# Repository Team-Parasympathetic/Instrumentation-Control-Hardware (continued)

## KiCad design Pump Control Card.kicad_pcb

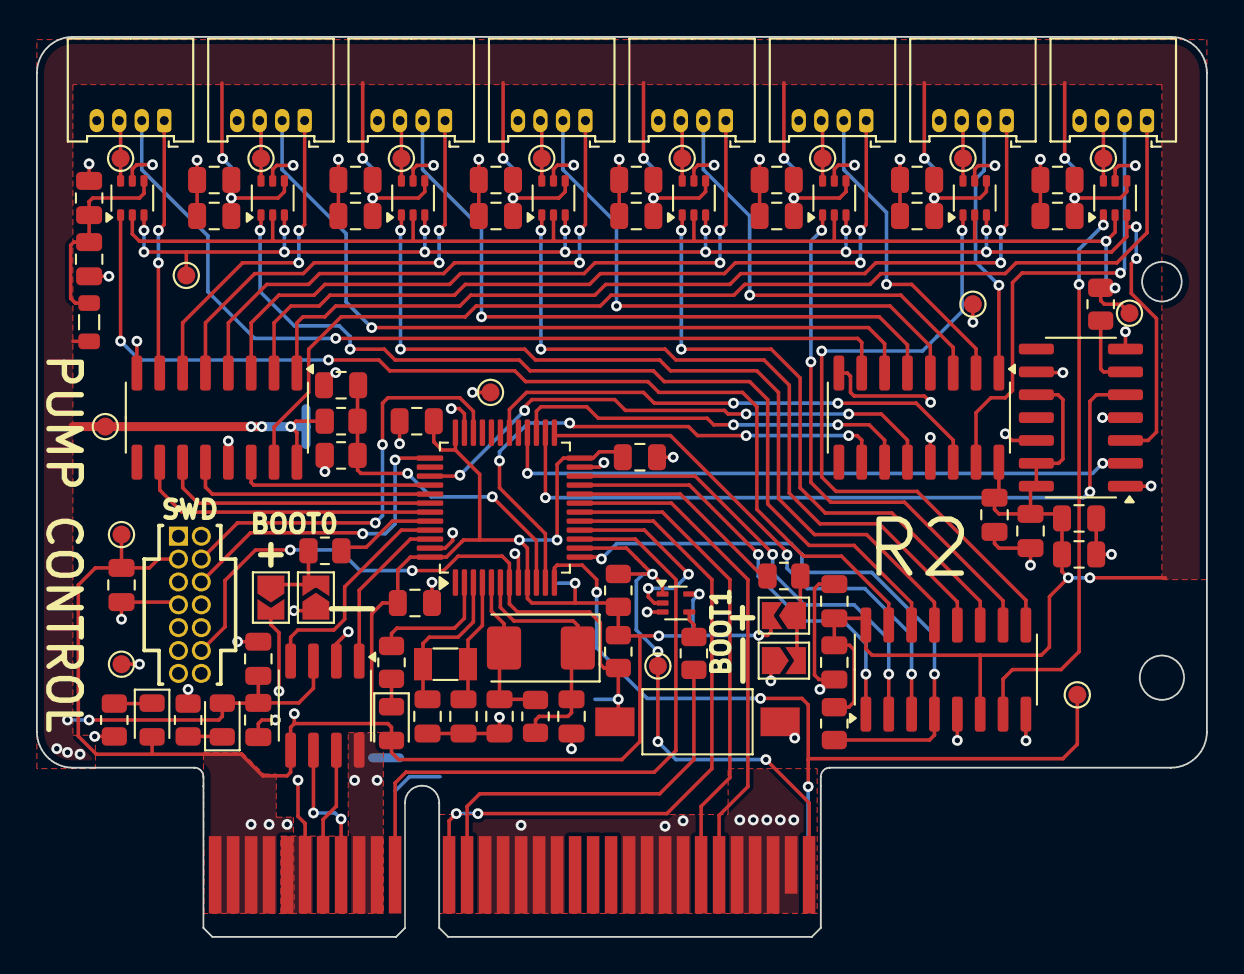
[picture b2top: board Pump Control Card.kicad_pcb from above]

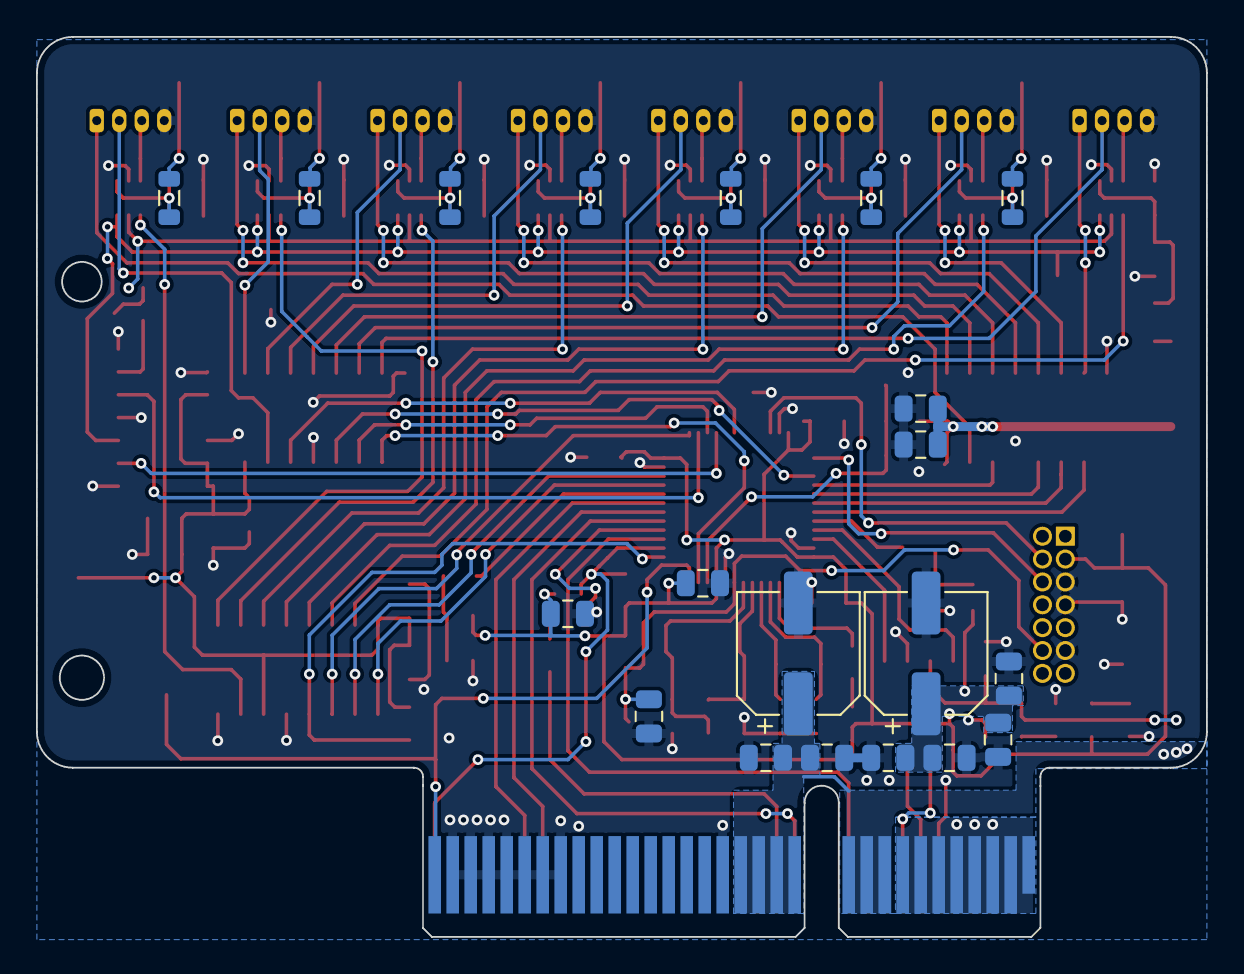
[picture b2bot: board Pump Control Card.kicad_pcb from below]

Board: 2 copper layers, 65.0 x 50.0 mm, 119 parts (20 on the bottom side), 89 nets.

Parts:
C1, C2, C6, C8, C10, C14, C16, C21, C22, C23, C25, C27, C29, C31, C33, C35, C37, C39, C41, C88, C91, C125: 0.1uF; C_0805_2012Metric
C3: 47nF; C_0805_2012Metric
C7, C9, C11, C15, C24, C26, C28, C30, C32, C34, C36, C38, C40, C89, C93: 1uF; C_0805_2012Metric
C12, C13: 10uF; C_0805_2012Metric
C17, C18, C19, C20: 20pF; C_0805_2012Metric
C90, C96: 47uF; CP_Elec_6.3x5.9
D2, D3, D4: LED; LED_0805_2012Metric
FB1, FB2, FB3, FB4, FB5, FB6, FB7, FB8: FerriteBead_Small; L_0805_2012Metric
J1, J2, J4, J5, J6, J7, J8, J9: Conn_01x04; Molex_PicoBlade_53048-0410_1x04_P1.25mm_Horizontal
J3: FTSH-107-01-L-D-K; SAMTEC_FTSH-107-01-L-D-K
J10: 10018784-10201TLF; BUS_PCIexpress_x4
JP5, JP6, JP7, JP8: SolderJumper_2_Open; SolderJumper-2_P1.3mm_Open_TrianglePad1.0x1.5mm
R1, R6: 22R; R_0805_2012Metric
R2, R11: 510R; R_0805_2012Metric
R3: 1K; R_0805_2012Metric
R4, R5: 4.7K; R_0805_2012Metric
R7: 33K; R_0805_2012Metric
R8: 20K; R_0805_2012Metric
R12: 10K; R_0805_2012Metric
R13, R14: 100K; R_0805_2012Metric
R15: 1M; R_0805_2012Metric
SW2: SW_Push; SW_SPST_FSMSM
TP1, TP2, TP3, TP4, TP5, TP6, TP7, TP8, TP9, TP10, TP11, TP12, TP13, TP14, TP15, TP16, TP17: TestPoint; TestPoint_Pad_D1.0mm
U1: MCP2562-E-SN; SOIC-8_3.9x4.9mm_P1.27mm
U2: SN74LVC1G125DRL; Texas_R-PDSO-N5_DRL-5
U3, U5: 74HCT595; SOIC-16_3.9x9.9mm_P1.27mm
U4: STM32F103C8Tx; LQFP-48_7x7mm_P0.5mm
U6: 74AHCT125; SOIC-14_3.9x8.7mm_P1.27mm
U7, U9, U10, U11, U12, U13, U14, U15: DAC7311xDCK; SOT-363_SC-70-6
U8: 74HCT138; SOIC-16_3.9x9.9mm_P1.27mm
Y3: 8MHz; Crystal_SMD_Abracon_ABM3-2Pin_5.0x3.2mm
Y4: 32.768K; Crystal_SMD_3215-2Pin_3.2x1.5mm

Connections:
+3V3: C2.1, C6.2, C13.1, C16.1, C21.1, C22.1, C23.1, C88.1, C89.1, C90.1, C125.1, D2.2 (A), D4.2 (A), J3.03, J10.A1, J10.A2, J10.A3, J10.A4, J10.A5, J10.A6, J10.A7, J10.A8, J10.B1, J10.B2, J10.B3, J10.B4, JP5.2 (B), JP7.2 (B), R4.1, R12.1, TP3.1, U1.5 (Vio), U2.5 (VCC), U4.9 (VDDA), U4.24 (VDD), U4.36 (VDD), U4.48 (VDD)
+5V: C1.1, C7.1, C8.1, C9.1, C10.1, C12.1, C24.1, C25.1, C26.1, C27.1, C91.1, C93.1, C96.1, D3.2 (A), FB1.1, FB2.1, FB3.1, FB4.1, FB5.1, FB6.1, FB7.1, FB8.1, J10.A9, J10.A10, J10.A11, J10.A12, J10.A13, J10.A14, J10.A15, R5.1, R7.1, TP2.1, U1.3 (VDD), U3.16 (VCC), U5.16 (VCC), U6.10, U6.13, U6.14 (VCC), U8.6 (E2), U8.16 (VCC)
/CAN_H: J10.B7, U1.7 (CANH)
/CAN_L: J10.B8, U1.6 (CANL)
/CS: J10.B32, R4.2, TP16.1, U2.1, U4.14 (PA4)
/DAC_Array/CS_1: U8.15 (~Y0), U15.1 (~SYNC)
/DAC_Array/CS_2: U8.14 (~Y1), U14.1 (~SYNC)
/DAC_Array/CS_3: U8.13 (~Y2), U13.1 (~SYNC)
/DAC_Array/CS_4: U8.12 (~Y3), U12.1 (~SYNC)
/DAC_Array/CS_5: U8.11 (~Y4), U11.1 (~SYNC)
/DAC_Array/CS_6: U8.10 (~Y5), U10.1 (~SYNC)
/DAC_Array/CS_7: U8.9 (~Y6), U9.1 (~SYNC)
/DAC_Array/CS_8: U7.1 (~SYNC), U8.7 (~Y7)
/DIR_1: J9.2, U5.15 (QA)
/DIR_2: J8.2, U5.1 (QB)
/DIR_3: J7.2, U5.2 (QC)
/DIR_4: J6.2, U5.3 (QD)
/DIR_5: J5.2, U5.4 (QE)
/DIR_6: J4.2, U5.5 (QF)
/DIR_7: J2.2, U5.6 (QG)
/DIR_8: J1.2, U5.7 (QH)
/Decoder/A0: U4.21 (PB10), U8.1 (A0)
/Decoder/A1: U4.22 (PB11), U8.2 (A1)
/Decoder/A2: U4.25 (PB12), U8.3 (A2)
/Decoder/EN: R5.2, U4.13 (PA3), U8.4 (~E0)
/EN_1: J9.1, U3.15 (QA)
/EN_2: J8.1, U3.1 (QB)
/EN_3: J7.1, U3.2 (QC)
/EN_4: J6.1, U3.3 (QD)
/EN_5: J5.1, U3.4 (QE)
/EN_6: J4.1, U3.5 (QF)
/EN_7: J2.1, U3.6 (QG)
/EN_8: J1.1, U3.7 (QH)
/IRQ: J10.A32, TP17.1, U4.12 (PA2)
/Level Shifter/IN0: U4.28 (PB15), U6.2
/Level Shifter/IN1: U4.26 (PB13), U6.5
/Level Shifter/OUT1: R6.1, U6.6
/MCU/CANRX: U1.4 (RXD), U4.45 (PB8)
/MCU/CANTX: U1.1 (TXD), U4.46 (PB9)
/MCU/MISO_1: U2.2, U4.16 (PA6)
/MCU/MOSI_1: J10.B12, U4.17 (PA7)
/MCU/NRST: C15.1, J3.12, R12.2, SW2.2, U4.7 (NRST)
/MCU/PA1: U4.11 (PA1), U5.10 (~SRCLR)
/MCU/PA9: U4.30 (PA9), U5.14 (SER)
/MCU/PB3: U4.39 (PB3), U5.12 (RCLK)
/MCU/PB4: U3.14 (SER), U4.40 (PB4)
/MCU/PB5: U3.12 (RCLK), U4.41 (PB5)
/MCU/PB6: U3.11 (SRCLK), U4.42 (PB6)
/MCU/PB7: U3.10 (~SRCLR), U4.43 (PB7)
/MCU/PB14: U4.27 (PB14), U5.11 (SRCLK)
/MCU/PC13: R11.2, U4.2 (PC13)
/MCU/SCK_1: J10.B11, U4.15 (PA5)
/MCU/SWCLK: J3.06, U4.37 (PA14)
/MCU/SWDIO: J3.04, U4.34 (PA13)
/MCU/VSENS: C3.1, R7.2, R8.1, U4.10 (PA0)
/PCIE/MISO_1: J10.B13, R1.1
/RST: J10.B26, U4.18 (PB0)
/SPD_1: J9.3, TP4.1, U7.6 (VOUT)
/SPD_2: J8.3, TP5.1, U9.6 (VOUT)
/SPD_3: J7.3, TP6.1, U10.6 (VOUT)
/SPD_4: J6.3, TP7.1, U11.6 (VOUT)
/SPD_5: J5.3, TP8.1, U12.6 (VOUT)
/SPD_6: J4.3, TP9.1, U13.6 (VOUT)
/SPD_7: J2.3, TP10.1, U14.6 (VOUT)
/SPD_8: J1.3, TP11.1, U15.6 (VOUT)
/SPI2_MOSI: TP12.1, U6.3, U7.3 (DIN), U9.3 (DIN), U10.3 (DIN), U11.3 (DIN), U12.3 (DIN), U13.3 (DIN), U14.3 (DIN), U15.3 (DIN)
/SPI2_SCK: R6.2, TP13.1, U7.2 (SCLK), U9.2 (SCLK), U10.2 (SCLK), U11.2 (SCLK), U12.2 (SCLK), U13.2 (SCLK), U14.2 (SCLK), U15.2 (SCLK)
/SYNC: J10.B27, U4.19 (PB1)
/Tristate/OUT: R1.2, U2.4
GND: C1.2, C2.2, C3.2, C6.1, C7.2, C8.2, C9.2, C10.2, C11.2, C12.2, C13.2, C14.2, C15.2, C16.2, C17.1, C18.1, C19.1, C20.1, C21.2, C22.2, C23.2, C24.2, C25.2, C26.2, C27.2, C28.2, C29.2, C30.2, C31.2, C32.2, C33.2, C34.2, C35.2, C36.2, C37.2, C38.2, C39.2, C40.2, C41.2, C88.2, C89.2, C90.2, C91.2, C93.2, C96.2, C125.2, J1.4, J2.4, J3.05, J3.07, J3.11, J4.4, J5.4, J6.4, J7.4, J8.4, J9.4, J10.A16, J10.A25, J10.A26, J10.A27, J10.A28, J10.A29, J10.A30, J10.A31, J10.B5, J10.B6, J10.B9, J10.B10, J10.B14, J10.B15, J10.B16, J10.B17, J10.B18, J10.B22, J10.B23, J10.B24, J10.B25, J10.B28, J10.B29, J10.B30, J10.B31, JP6.1 (A), JP8.1 (A), R2.2, R3.2, R8.2, SW2.1, TP1.1, TP14.1, TP15.1, U1.2 (VSS), U1.8 (STBY), U2.3 (GND), U3.8 (GND), U3.13 (~OE), U4.8 (VSSA), U4.23 (VSS), U4.35 (VSS), U4.47 (VSS), U5.8 (GND), U5.13 (~OE), U6.1, U6.4, U6.7 (GND), U6.9, U6.12, U7.5 (GND), U8.5 (~E1), U8.8 (GND), U9.5 (GND), U10.5 (GND), U11.5 (GND), U12.5 (GND), U13.5 (GND), U14.5 (GND), U15.5 (GND)
unnamed: D2.1 (K), R2.1
unnamed: D3.1 (K), R3.1
unnamed: D4.1 (K), R11.1
unnamed: JP5.1 (A), JP6.2 (B), R14.1
unnamed: JP7.1 (A), JP8.2 (B), R13.1
unnamed: R13.2, U4.44 (BOOT0)
unnamed: R14.2, U4.20 (PB2)
unnamed: C19.2, U4.3 (PC14), Y4.2
unnamed: C20.2, U4.4 (PC15), Y4.1
unnamed: C17.2, R15.1, U4.5 (PD0), Y3.2
unnamed: C18.2, R15.2, U4.6 (PD1), Y3.1
unnamed: C11.1, C14.1, FB1.2, U7.4 (AVDD/AVREF)
unnamed: C28.1, C29.1, FB2.2, U9.4 (AVDD/AVREF)
unnamed: C30.1, C31.1, FB3.2, U10.4 (AVDD/AVREF)
unnamed: C32.1, C33.1, FB4.2, U11.4 (AVDD/AVREF)
unnamed: C34.1, C35.1, FB5.2, U12.4 (AVDD/AVREF)
unnamed: C36.1, C37.1, FB6.2, U13.4 (AVDD/AVREF)
unnamed: C38.1, C39.1, FB7.2, U14.4 (AVDD/AVREF)
unnamed: C40.1, C41.1, FB8.2, U15.4 (AVDD/AVREF)

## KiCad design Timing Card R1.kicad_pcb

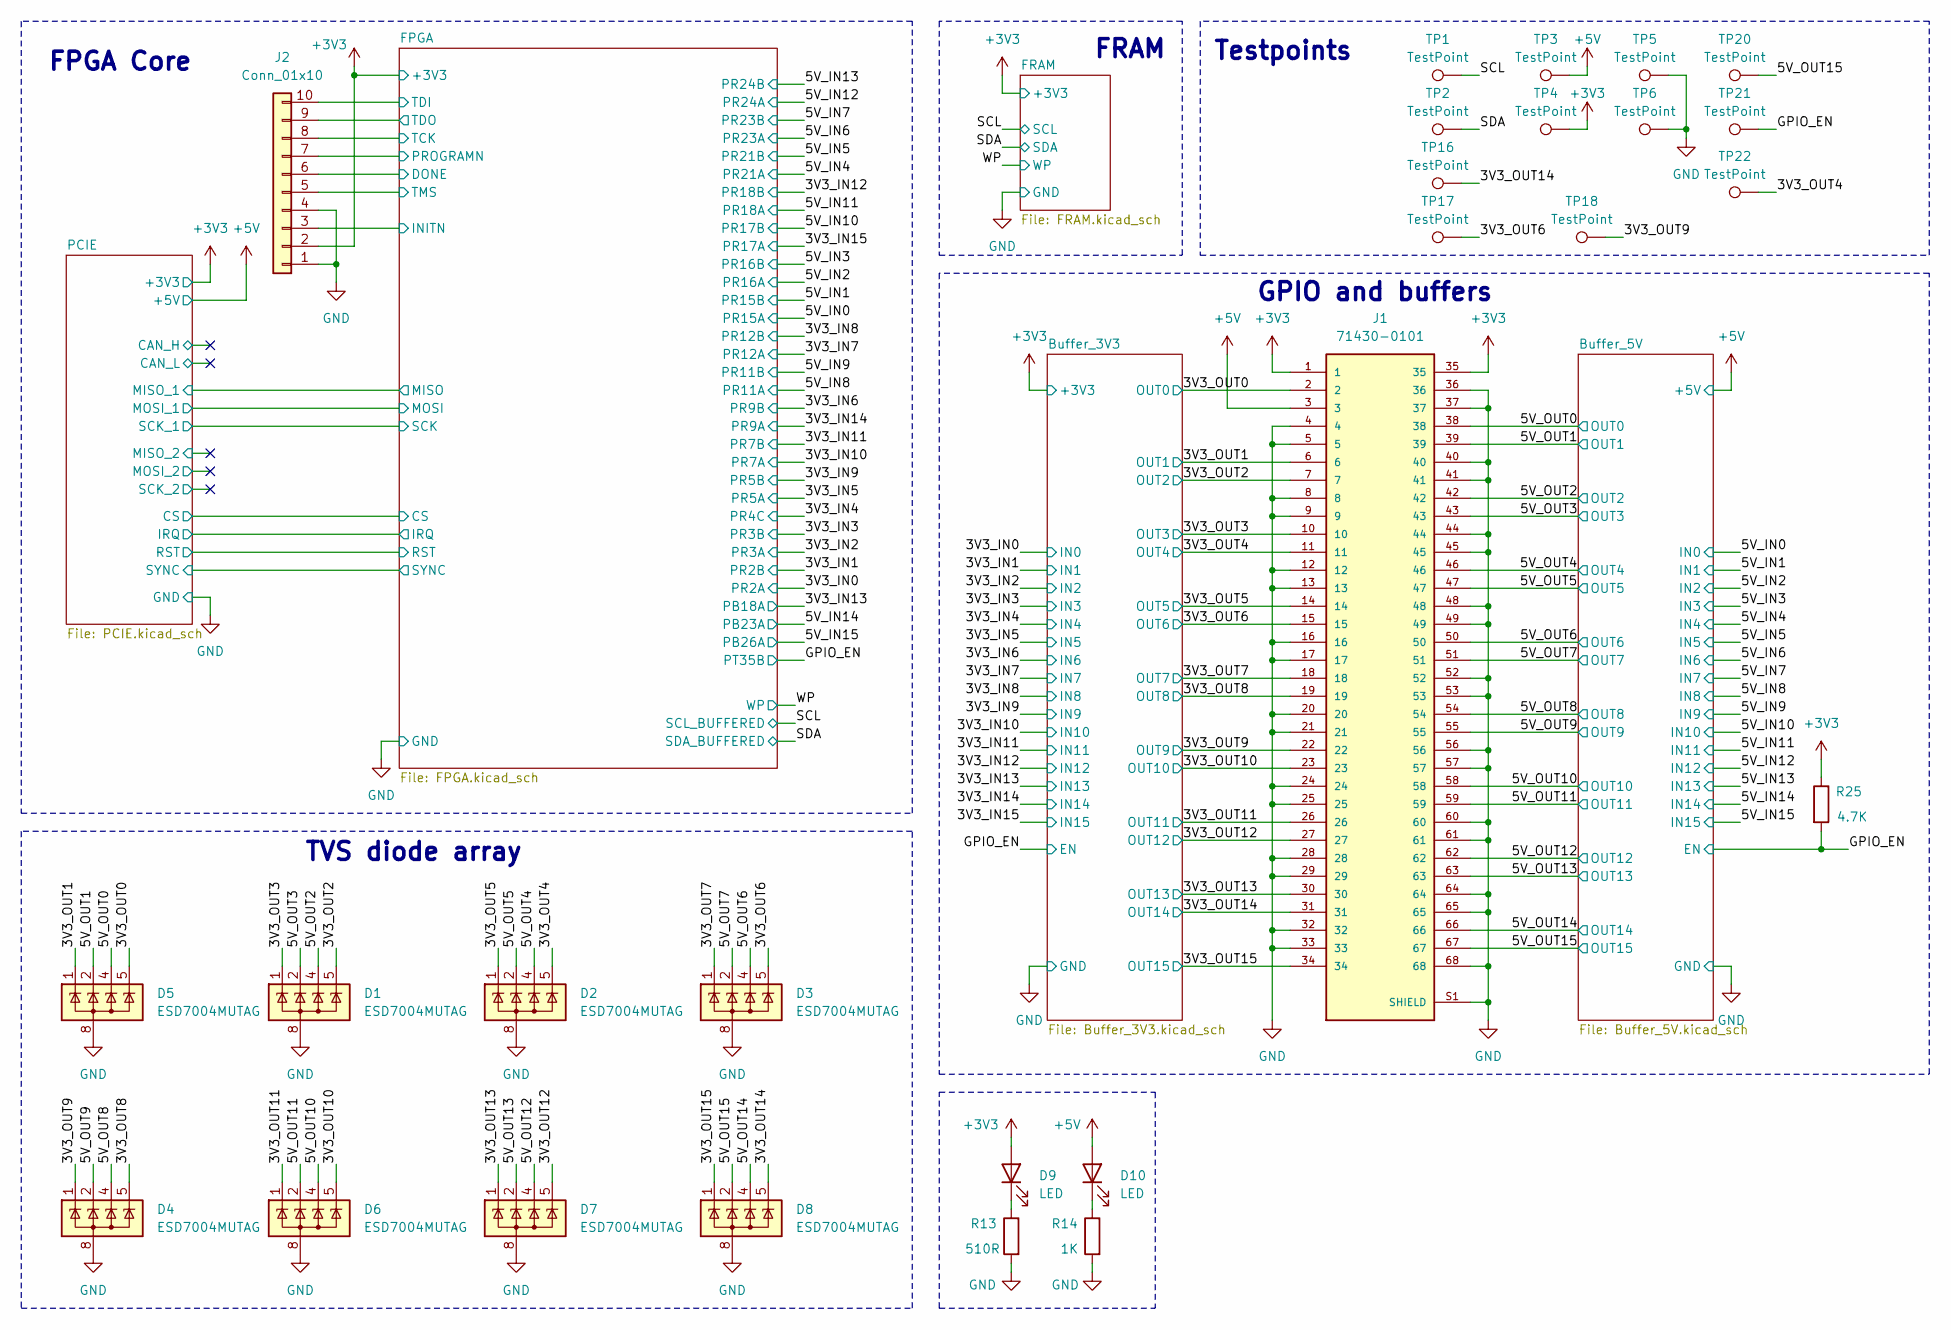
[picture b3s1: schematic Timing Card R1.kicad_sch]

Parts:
D1, D2, D3, D4, D5, D6, D7, D8: ESD7004MUTAG; Diodes_UDFN-10_1x2.5mm_P0.5mm_Modified
D9, D10: LED; LED_0805_2012Metric
J1: 71430-0101; MOLEX_71430-0101; PARTREV N
J2: Conn_01x10; PinHeader_2x05_P2.54mm_Vertical
R13: 510R; R_0805_2012Metric
R14: 1K; R_0805_2012Metric
R25: 4.7K; R_0805_2012Metric
TP1, TP2, TP3, TP4, TP5, TP6, TP16, TP17, TP18, TP20, TP21, TP22: TestPoint; TestPoint_Pad_D1.0mm

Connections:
+5V: D10.2 (A), J1.3, TP3.1; also elsewhere on the board
/3V3_OUT0: D5.5 (K), J1.2; also elsewhere on the board
/3V3_OUT1: D5.1 (K), J1.6; also elsewhere on the board
/3V3_OUT2: D1.5 (K), J1.7; also elsewhere on the board
/3V3_OUT3: D1.1 (K), J1.10; also elsewhere on the board
/3V3_OUT4: D2.5 (K), J1.11, TP22.1; also elsewhere on the board
/3V3_OUT5: D2.1 (K), J1.14; also elsewhere on the board
/3V3_OUT6: D3.5 (K), J1.15, TP17.1; also elsewhere on the board
/3V3_OUT7: D3.1 (K), J1.18; also elsewhere on the board
/3V3_OUT8: D4.5 (K), J1.19; also elsewhere on the board
/3V3_OUT9: D4.1 (K), J1.22, TP18.1; also elsewhere on the board
/3V3_OUT10: D6.5 (K), J1.23; also elsewhere on the board
/3V3_OUT11: D6.1 (K), J1.26; also elsewhere on the board
/3V3_OUT12: D7.5 (K), J1.27; also elsewhere on the board
/3V3_OUT13: D7.1 (K), J1.30; also elsewhere on the board
/3V3_OUT14: D8.5 (K), J1.31, TP16.1; also elsewhere on the board
/3V3_OUT15: D8.1 (K), J1.34; also elsewhere on the board
/5V_OUT0: D5.4 (K), J1.38; also elsewhere on the board
/5V_OUT1: D5.2 (K), J1.39; also elsewhere on the board
/5V_OUT2: D1.4 (K), J1.42; also elsewhere on the board
/5V_OUT3: D1.2 (K), J1.43; also elsewhere on the board
/5V_OUT4: D2.4 (K), J1.46; also elsewhere on the board
/5V_OUT5: D2.2 (K), J1.47; also elsewhere on the board
/5V_OUT6: D3.4 (K), J1.50; also elsewhere on the board
/5V_OUT7: D3.2 (K), J1.51; also elsewhere on the board
/5V_OUT8: D4.4 (K), J1.54; also elsewhere on the board
/5V_OUT9: D4.2 (K), J1.55; also elsewhere on the board
/5V_OUT10: D6.4 (K), J1.58; also elsewhere on the board
/5V_OUT11: D6.2 (K), J1.59; also elsewhere on the board
/5V_OUT12: D7.4 (K), J1.62; also elsewhere on the board
/5V_OUT13: D7.2 (K), J1.63; also elsewhere on the board
/5V_OUT14: D8.4 (K), J1.66; also elsewhere on the board
/5V_OUT15: D8.2 (K), J1.67, TP20.1; also elsewhere on the board
/FPGA/DONE: J2.6; also elsewhere on the board
/FPGA/INITN: J2.3; also elsewhere on the board
/FPGA/PROGRAMN: J2.7; also elsewhere on the board
/FPGA/TCK: J2.8; also elsewhere on the board
/FPGA/TDI: J2.10; also elsewhere on the board
/FPGA/TDO: J2.9; also elsewhere on the board
/FPGA/TMS: J2.5; also elsewhere on the board
/GPIO_EN: R25.2, TP21.1; also elsewhere on the board
/SCL: TP1.1; also elsewhere on the board
/SDA: TP2.1; also elsewhere on the board
unnamed: D9.1 (K), R13.1
unnamed: D10.1 (K), R14.1

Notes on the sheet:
FRAM
FPGA Core
Testpoints
GPIO and buffers
TVS diode array

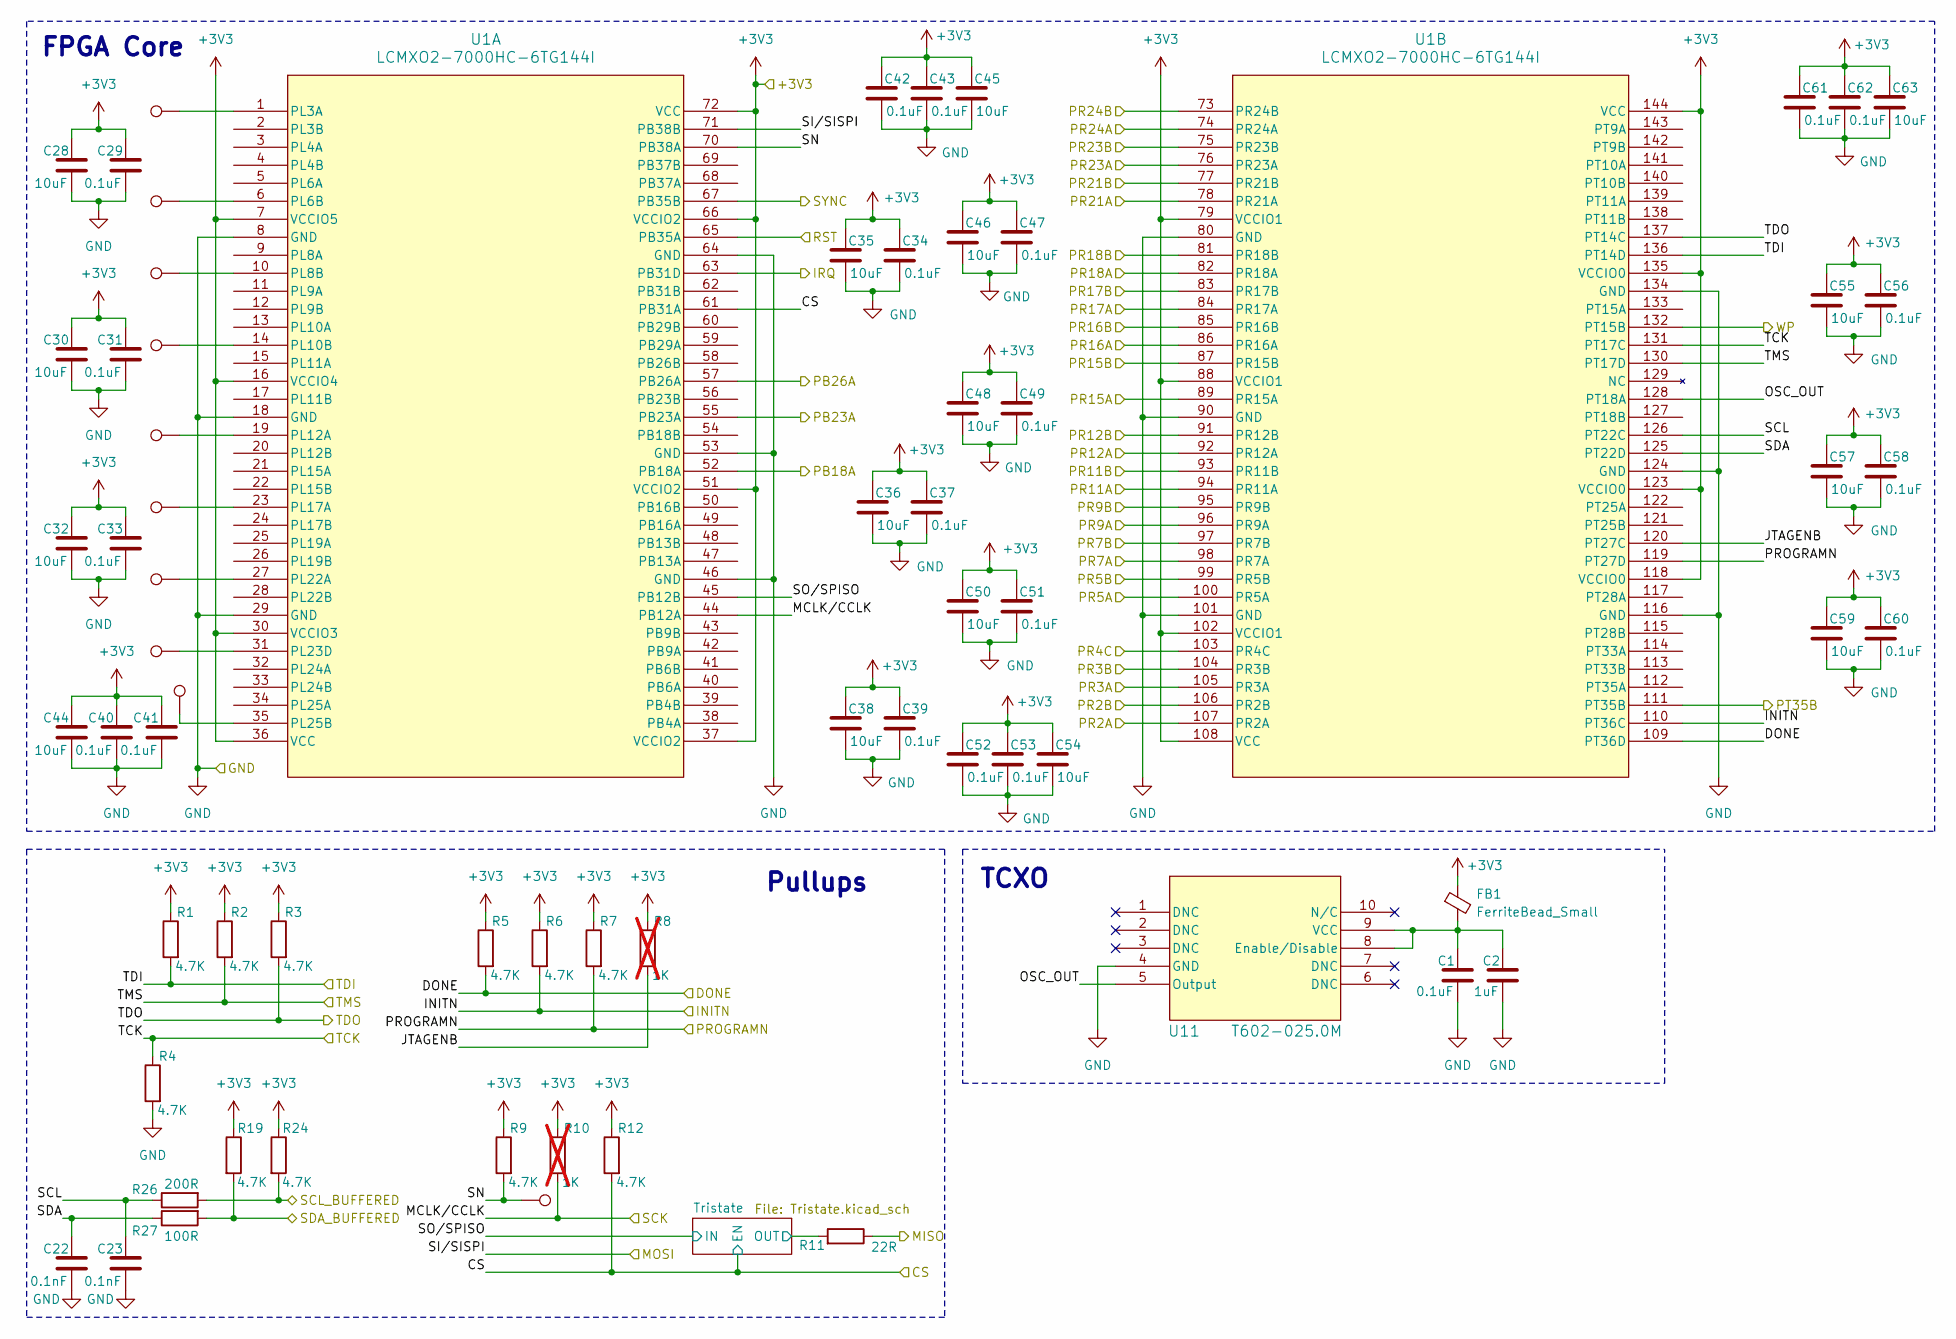
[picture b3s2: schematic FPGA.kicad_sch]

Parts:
C1: 0.1uF; C_0805_2012Metric
C2: 1uF; C_0805_2012Metric
C22, C23: 0.1nF; C_0805_2012Metric
C28, C30, C32, C35, C36, C38, C44, C45, C46, C48, C50, C54, C55, C57, C59, C63: 10uF; C_0603_1608Metric
C29, C31, C33, C34, C37, C39, C40, C41, C42, C43, C47, C49, C51, C52, C53, C56, C58, C60, C61, C62: 0.1uF; C_0603_1608Metric
FB1: FerriteBead_Small; L_0805_2012Metric
R1, R2, R3, R4, R5, R6, R7, R9, R12, R19, R24: 4.7K; R_0805_2012Metric
R8, R10: 1K; R_0805_2012Metric; not fitted
R11: 22R; R_0805_2012Metric
R26: 200R; R_0805_2012Metric
R27: 100R; R_0805_2012Metric
TP7, TP8, TP9, TP10, TP11, TP12, TP13, TP14, TP15: TestPoint; TestPoint_Pad_1.0x1.0mm
TP19: TestPoint; TestPoint_Pad_D1.0mm
U1: LCMXO2-7000HC-6TG144I; TQFP144_LAT
U11: T602-025.0M; T602-025.0M_CNW

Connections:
/3V3_IN0: U1.107 (PR2A); also elsewhere on the board
/3V3_IN1: U1.106 (PR2B); also elsewhere on the board
/3V3_IN2: U1.105 (PR3A); also elsewhere on the board
/3V3_IN3: U1.104 (PR3B); also elsewhere on the board
/3V3_IN4: U1.103 (PR4C); also elsewhere on the board
/3V3_IN5: U1.100 (PR5A); also elsewhere on the board
/3V3_IN6: U1.95 (PR9B); also elsewhere on the board
/3V3_IN7: U1.92 (PR12A); also elsewhere on the board
/3V3_IN8: U1.91 (PR12B); also elsewhere on the board
/3V3_IN9: U1.99 (PR5B); also elsewhere on the board
/3V3_IN10: U1.98 (PR7A); also elsewhere on the board
/3V3_IN11: U1.97 (PR7B); also elsewhere on the board
/3V3_IN12: U1.81 (PR18B); also elsewhere on the board
/3V3_IN13: U1.52 (PB18A); also elsewhere on the board
/3V3_IN14: U1.96 (PR9A); also elsewhere on the board
/3V3_IN15: U1.84 (PR17A); also elsewhere on the board
/5V_IN0: U1.89 (PR15A); also elsewhere on the board
/5V_IN1: U1.87 (PR15B); also elsewhere on the board
/5V_IN2: U1.86 (PR16A); also elsewhere on the board
/5V_IN3: U1.85 (PR16B); also elsewhere on the board
/5V_IN4: U1.78 (PR21A); also elsewhere on the board
/5V_IN5: U1.77 (PR21B); also elsewhere on the board
/5V_IN6: U1.76 (PR23A); also elsewhere on the board
/5V_IN7: U1.75 (PR23B); also elsewhere on the board
/5V_IN8: U1.94 (PR11A); also elsewhere on the board
/5V_IN9: U1.93 (PR11B); also elsewhere on the board
/5V_IN10: U1.83 (PR17B); also elsewhere on the board
/5V_IN11: U1.82 (PR18A); also elsewhere on the board
/5V_IN12: U1.74 (PR24A); also elsewhere on the board
/5V_IN13: U1.73 (PR24B); also elsewhere on the board
/5V_IN14: U1.55 (PB23A); also elsewhere on the board
/5V_IN15: U1.57 (PB26A); also elsewhere on the board
/FPGA/CS: R12.2, U1.61 (PB31A); also elsewhere on the board
/FPGA/DONE: R5.2, U1.109 (PT36D); also elsewhere on the board
/FPGA/INITN: R6.2, U1.110 (PT36C); also elsewhere on the board
/FPGA/IRQ: U1.63 (PB31D); also elsewhere on the board
/FPGA/JTAGENB: R8.2, U1.120 (PT27C)
/FPGA/MCLK/CCLK: R10.2, U1.44 (PB12A); also elsewhere on the board
/FPGA/MISO: R11.1; also elsewhere on the board
/FPGA/OSC_OUT: U1.128 (PT18A), U11.5 (Output)
/FPGA/PROGRAMN: R7.2, U1.119 (PT27D); also elsewhere on the board
/FPGA/RST: U1.65 (PB35A); also elsewhere on the board
/FPGA/SCL: C23.1, R26.1, U1.126 (PT22C)
/FPGA/SDA: C22.1, R27.1, U1.125 (PT22D)
/FPGA/SI/SISPI: U1.71 (PB38B); also elsewhere on the board
/FPGA/SN: R9.2, TP19.1, U1.70 (PB38A)
/FPGA/SO/SPISO: U1.45 (PB12B); also elsewhere on the board
/FPGA/SYNC: U1.67 (PB35B); also elsewhere on the board
/FPGA/TCK: R4.1, U1.131 (PT17C); also elsewhere on the board
/FPGA/TDI: R1.2, U1.136 (PT14D); also elsewhere on the board
/FPGA/TDO: R3.2, U1.137 (PT14C); also elsewhere on the board
/FPGA/TMS: R2.2, U1.130 (PT17D); also elsewhere on the board
/FPGA/Tristate/OUT: R11.2; also elsewhere on the board
/GPIO_EN: U1.111 (PT35B); also elsewhere on the board
/SCL: R24.2, R26.2; also elsewhere on the board
/SDA: R19.2, R27.2; also elsewhere on the board
/WP: U1.132 (PT15B); also elsewhere on the board
unnamed: TP7.1, U1.1 (PL3A)
unnamed: TP8.1, U1.6 (PL6B)
unnamed: TP9.1, U1.10 (PL8B)
unnamed: TP10.1, U1.14 (PL10B)
unnamed: TP11.1, U1.19 (PL12A)
unnamed: TP12.1, U1.23 (PL17A)
unnamed: TP13.1, U1.27 (PL22A)
unnamed: TP14.1, U1.31 (PL23D)
unnamed: TP15.1, U1.35 (PL25B)
unnamed: C1.1, C2.1, FB1.2, U11.8 (Enable/Disable), U11.9 (VCC)

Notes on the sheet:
TCXO
Pullups
FPGA Core

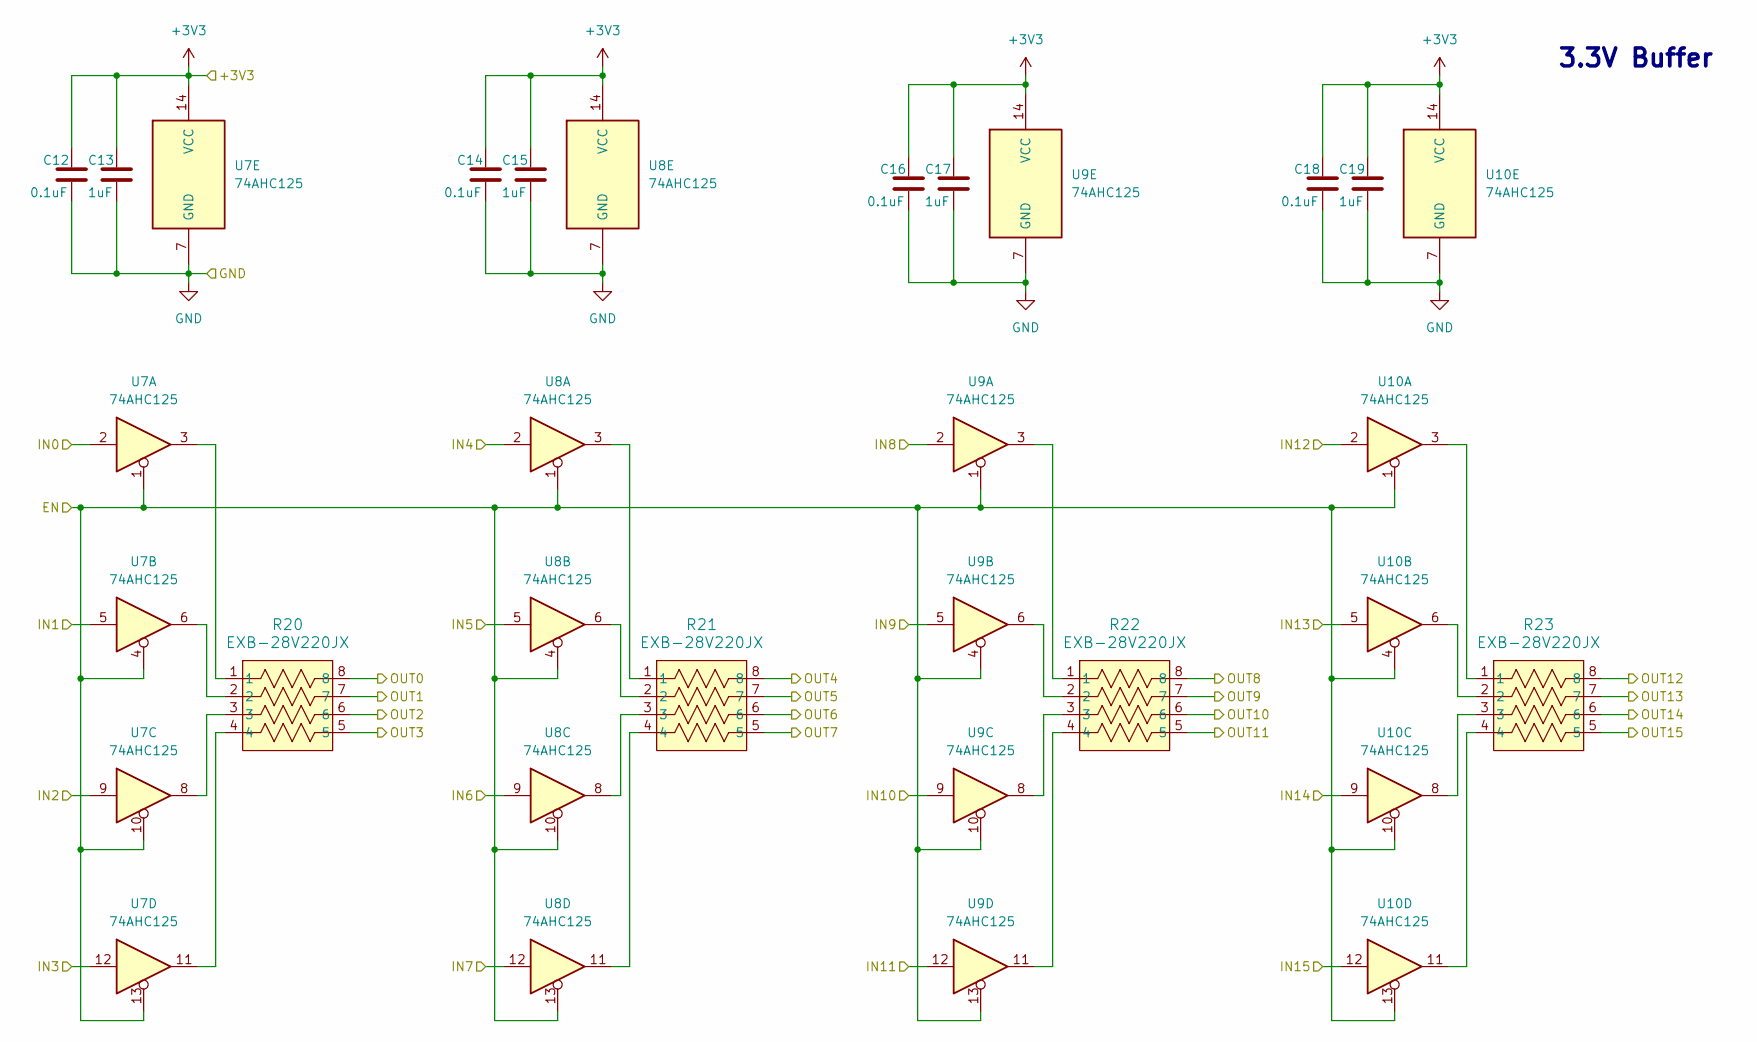
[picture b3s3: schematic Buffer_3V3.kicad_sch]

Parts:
C12, C14, C16, C18: 0.1uF; C_0805_2012Metric
C13, C15, C17, C19: 1uF; C_0805_2012Metric
R20, R21, R22, R23: EXB-28V220JX; EXB28V_PAN
U7, U8, U9, U10: 74AHC125; TSSOP-14_4.4x5mm_P0.65mm

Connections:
/3V3_IN0: U7.2; also elsewhere on the board
/3V3_IN1: U7.5; also elsewhere on the board
/3V3_IN2: U7.9; also elsewhere on the board
/3V3_IN3: U7.12; also elsewhere on the board
/3V3_IN4: U8.2; also elsewhere on the board
/3V3_IN5: U8.5; also elsewhere on the board
/3V3_IN6: U8.9; also elsewhere on the board
/3V3_IN7: U8.12; also elsewhere on the board
/3V3_IN8: U9.2; also elsewhere on the board
/3V3_IN9: U9.5; also elsewhere on the board
/3V3_IN10: U9.9; also elsewhere on the board
/3V3_IN11: U9.12; also elsewhere on the board
/3V3_IN12: U10.2; also elsewhere on the board
/3V3_IN13: U10.5; also elsewhere on the board
/3V3_IN14: U10.9; also elsewhere on the board
/3V3_IN15: U10.12; also elsewhere on the board
/3V3_OUT0: R20.8; also elsewhere on the board
/3V3_OUT1: R20.7; also elsewhere on the board
/3V3_OUT2: R20.6; also elsewhere on the board
/3V3_OUT3: R20.5; also elsewhere on the board
/3V3_OUT4: R21.8; also elsewhere on the board
/3V3_OUT5: R21.7; also elsewhere on the board
/3V3_OUT6: R21.6; also elsewhere on the board
/3V3_OUT7: R21.5; also elsewhere on the board
/3V3_OUT8: R22.8; also elsewhere on the board
/3V3_OUT9: R22.7; also elsewhere on the board
/3V3_OUT10: R22.6; also elsewhere on the board
/3V3_OUT11: R22.5; also elsewhere on the board
/3V3_OUT12: R23.8; also elsewhere on the board
/3V3_OUT13: R23.7; also elsewhere on the board
/3V3_OUT14: R23.6; also elsewhere on the board
/3V3_OUT15: R23.5; also elsewhere on the board
/GPIO_EN: U7.1, U7.4, U7.10, U7.13, U8.1, U8.4, U8.10, U8.13, U9.1, U9.4, U9.10, U9.13, U10.1, U10.4, U10.10, U10.13; also elsewhere on the board
unnamed: R20.1, U7.3
unnamed: R20.2, U7.6
unnamed: R20.3, U7.8
unnamed: R20.4, U7.11
unnamed: R21.1, U8.3
unnamed: R21.2, U8.6
unnamed: R21.3, U8.8
unnamed: R21.4, U8.11
unnamed: R22.1, U9.3
unnamed: R22.2, U9.6
unnamed: R22.3, U9.8
unnamed: R22.4, U9.11
unnamed: R23.1, U10.3
unnamed: R23.2, U10.6
unnamed: R23.3, U10.8
unnamed: R23.4, U10.11

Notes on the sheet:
3.3V Buffer

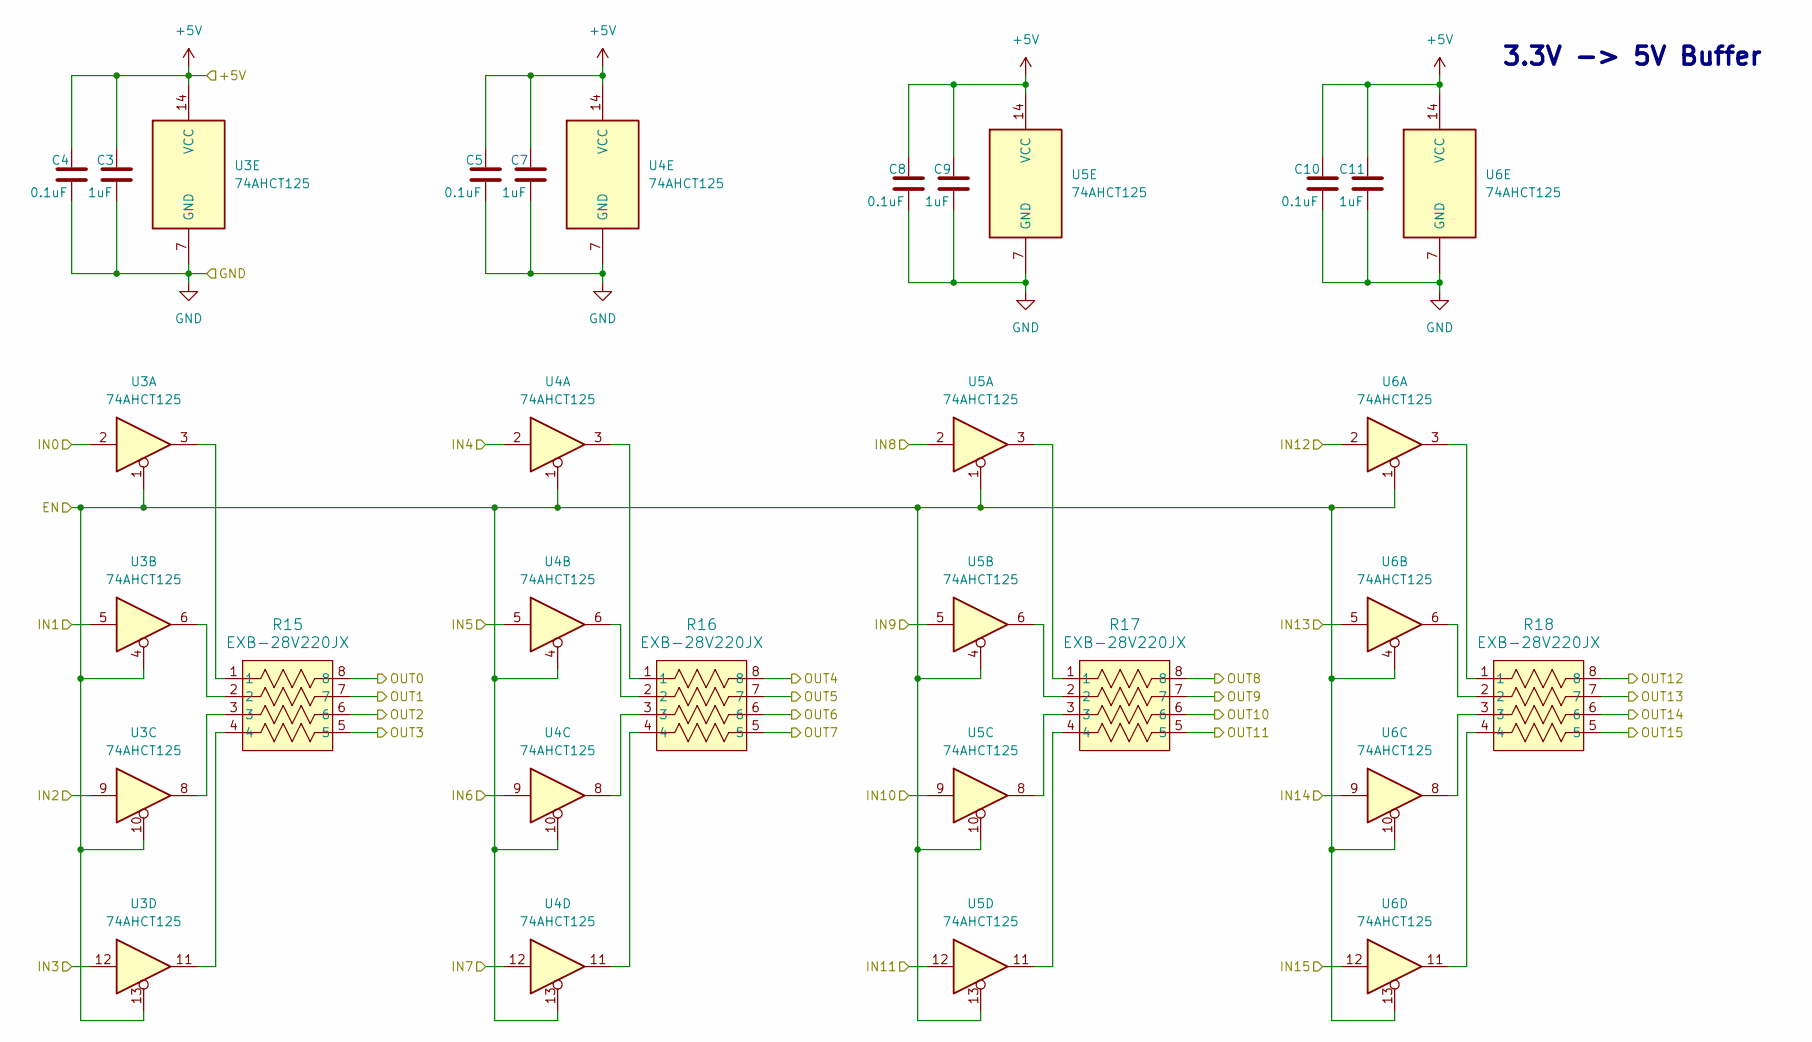
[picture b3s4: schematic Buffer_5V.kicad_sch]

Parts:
C3, C7, C9, C11: 1uF; C_0805_2012Metric
C4, C5, C8, C10: 0.1uF; C_0805_2012Metric
R15, R16, R17, R18: EXB-28V220JX; EXB28V_PAN
U3, U4, U5, U6: 74AHCT125; TSSOP-14_4.4x5mm_P0.65mm

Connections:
+5V: C3.1, C4.1, C5.1, C7.1, C8.1, C9.1, C10.1, C11.1, U3.14 (VCC), U4.14 (VCC), U5.14 (VCC), U6.14 (VCC); also elsewhere on the board
/5V_IN0: U3.2; also elsewhere on the board
/5V_IN1: U3.5; also elsewhere on the board
/5V_IN2: U3.9; also elsewhere on the board
/5V_IN3: U3.12; also elsewhere on the board
/5V_IN4: U4.2; also elsewhere on the board
/5V_IN5: U4.5; also elsewhere on the board
/5V_IN6: U4.9; also elsewhere on the board
/5V_IN7: U4.12; also elsewhere on the board
/5V_IN8: U5.2; also elsewhere on the board
/5V_IN9: U5.5; also elsewhere on the board
/5V_IN10: U5.9; also elsewhere on the board
/5V_IN11: U5.12; also elsewhere on the board
/5V_IN12: U6.2; also elsewhere on the board
/5V_IN13: U6.5; also elsewhere on the board
/5V_IN14: U6.9; also elsewhere on the board
/5V_IN15: U6.12; also elsewhere on the board
/5V_OUT0: R15.8; also elsewhere on the board
/5V_OUT1: R15.7; also elsewhere on the board
/5V_OUT2: R15.6; also elsewhere on the board
/5V_OUT3: R15.5; also elsewhere on the board
/5V_OUT4: R16.8; also elsewhere on the board
/5V_OUT5: R16.7; also elsewhere on the board
/5V_OUT6: R16.6; also elsewhere on the board
/5V_OUT7: R16.5; also elsewhere on the board
/5V_OUT8: R17.8; also elsewhere on the board
/5V_OUT9: R17.7; also elsewhere on the board
/5V_OUT10: R17.6; also elsewhere on the board
/5V_OUT11: R17.5; also elsewhere on the board
/5V_OUT12: R18.8; also elsewhere on the board
/5V_OUT13: R18.7; also elsewhere on the board
/5V_OUT14: R18.6; also elsewhere on the board
/5V_OUT15: R18.5; also elsewhere on the board
/GPIO_EN: U3.1, U3.4, U3.10, U3.13, U4.1, U4.4, U4.10, U4.13, U5.1, U5.4, U5.10, U5.13, U6.1, U6.4, U6.10, U6.13; also elsewhere on the board
unnamed: R15.1, U3.3
unnamed: R15.2, U3.6
unnamed: R15.3, U3.8
unnamed: R15.4, U3.11
unnamed: R16.1, U4.3
unnamed: R16.2, U4.6
unnamed: R16.3, U4.8
unnamed: R16.4, U4.11
unnamed: R17.1, U5.3
unnamed: R17.2, U5.6
unnamed: R17.3, U5.8
unnamed: R17.4, U5.11
unnamed: R18.1, U6.3
unnamed: R18.2, U6.6
unnamed: R18.3, U6.8
unnamed: R18.4, U6.11

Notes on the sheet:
3.3V -> 5V Buffer

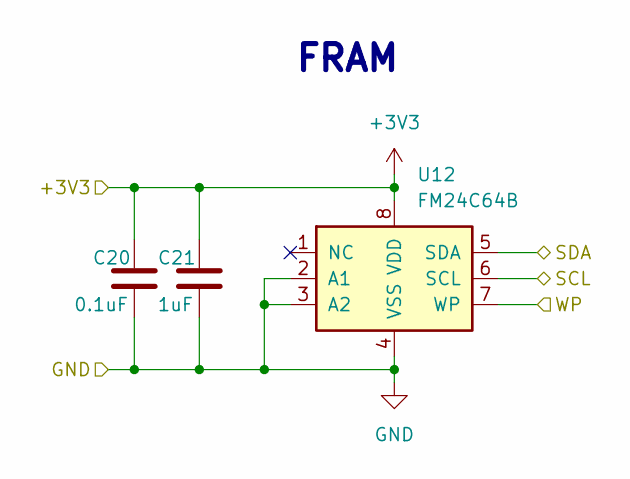
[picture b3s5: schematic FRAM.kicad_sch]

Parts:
C20: 0.1uF; C_0805_2012Metric
C21: 1uF; C_0805_2012Metric
U12: FM24C64B; SOIC-8_3.9x4.9mm_P1.27mm

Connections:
/SCL: U12.6 (SCL); also elsewhere on the board
/SDA: U12.5 (SDA); also elsewhere on the board
/WP: U12.7 (WP); also elsewhere on the board

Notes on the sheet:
FRAM
